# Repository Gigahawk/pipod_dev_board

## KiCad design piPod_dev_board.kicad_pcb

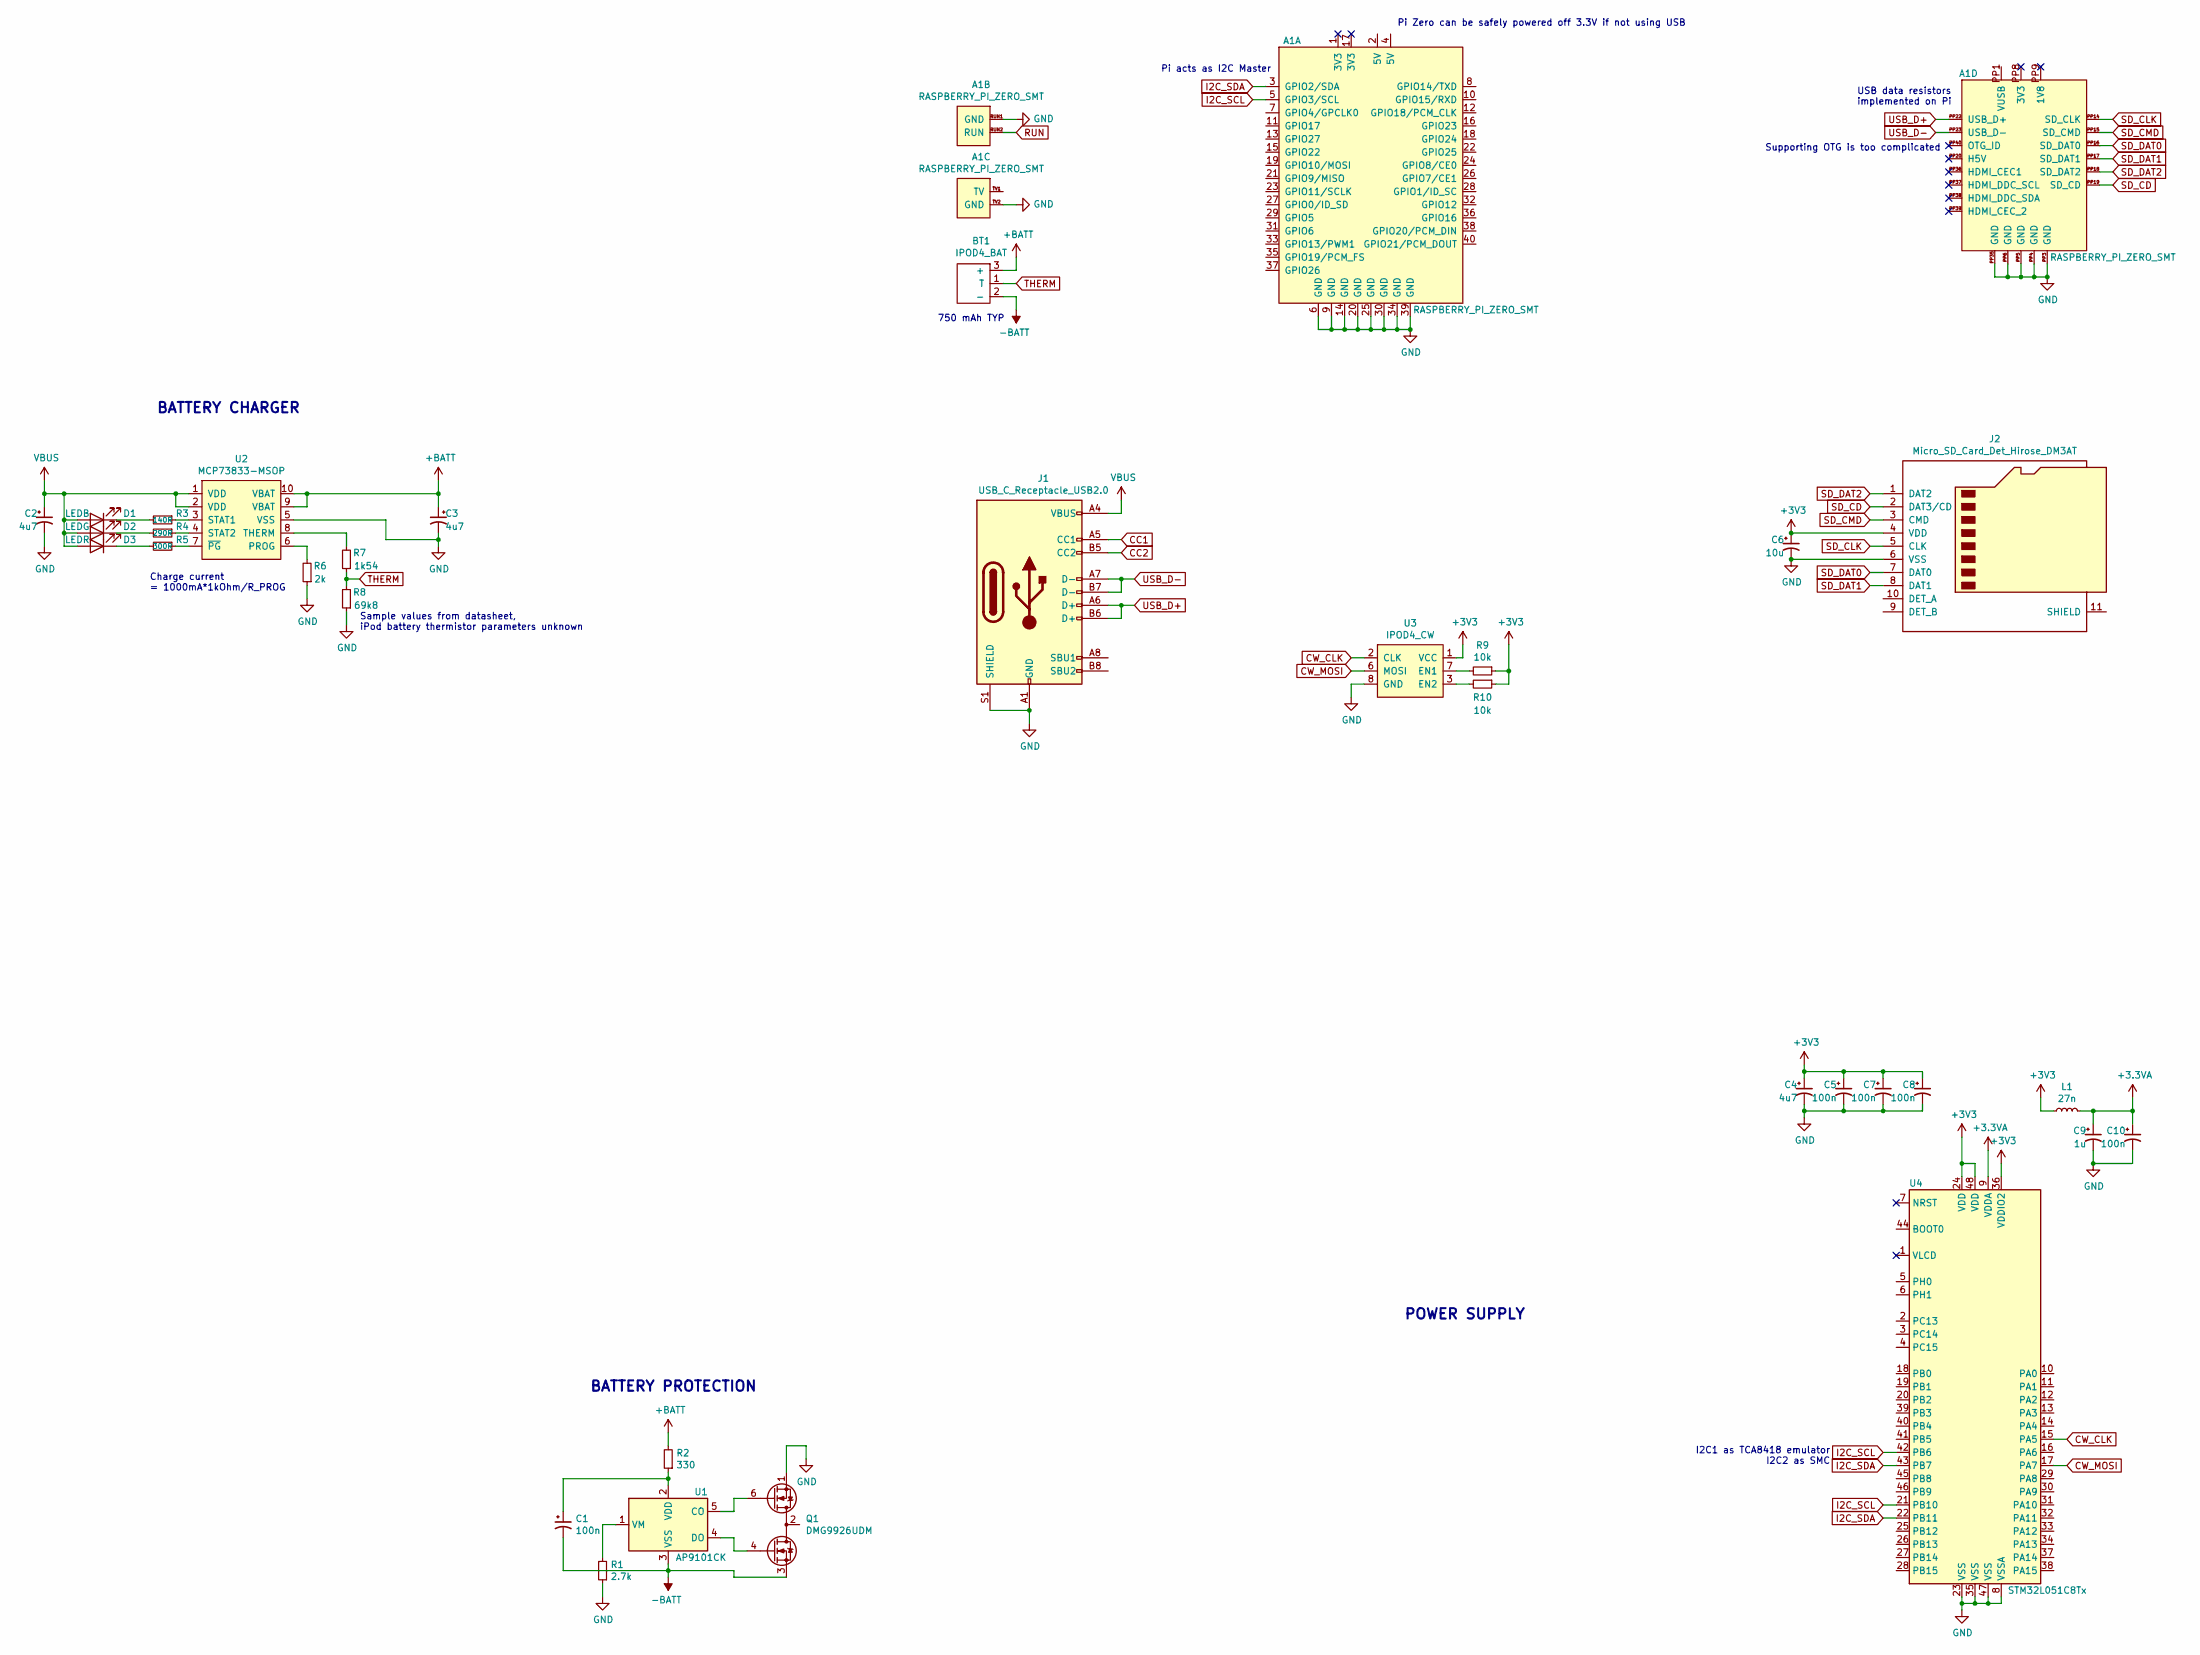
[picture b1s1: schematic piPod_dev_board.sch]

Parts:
A1: RASPBERRY_PI_ZERO_SMT; RASPI_ZERO_1_3_SMT_LOW_PROFILE
BT1: IPOD4_BAT; Molex_PicoBlade_53047-0310_1x03_P1.25mm_Vertical
C1, C5, C7, C8, C10: 100n; C_0805_2012Metric
C2, C3, C4: 4u7; C_0805_2012Metric
C6: 10u; C_0805_2012Metric
C9: 1u; C_0805_2012Metric
D1: LEDB
D2: LEDG
D3: LEDR
J1: USB_C_Receptacle_USB2.0; USB_C_Receptacle_GCT_USB4085
J2: Micro_SD_Card_Det_Hirose_DM3AT; microSD_HC_Hirose_DM3AT-SF-PEJM5
L1: 27n; L_0805_2012Metric
Q1: DMG9926UDM; SOT-23-6
R1: 2.7k; R_0805_2012Metric
R2: 330; R_0805_2012Metric
R3: 140R; R_0805_2012Metric
R4: 290R; R_0805_2012Metric
R5: 300R; R_0805_2012Metric
R6: 2k; R_0805_2012Metric
R7: 1k54; R_0805_2012Metric
R8: 69k8; R_0805_2012Metric
R9, R10: 10k; R_0805_2012Metric
U1: AP9101CK; SOT-23-5
U2: MCP73833-MSOP; MSOP-10_3x3mm_P0.5mm
U3: IPOD4_CW; SFV8R2STE1HLF
U4: STM32L051C8Tx; LQFP-48_7x7mm_P0.5mm

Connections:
+3.3VA: C9.1, C10.1, L1.2, U4.9 (VDDA)
+3V3: C4.1, C5.1, C6.1, C7.1, C8.1, J2.4 (VDD), L1.1, R9.1, R10.1, U3.1 (VCC), U4.24 (VDD), U4.36 (VDDIO2), U4.48 (VDD)
+BATT: BT1.3 (+), C3.1, R2.2, U2.9 (VBAT), U2.10 (VBAT)
-BATT: BT1.2 (-), C1.2, Q1.3 (S2), U1.3 (VSS)
CC1: J1.A5 (CC1)
CC2: J1.B5 (CC2)
CW_CLK: U3.2 (CLK), U4.15 (PA5)
CW_MOSI: U3.6 (MOSI), U4.17 (PA7)
GND: A1.6 (GND), A1.9 (GND), A1.14 (GND), A1.20 (GND), A1.25 (GND), A1.30 (GND), A1.34 (GND), A1.39 (GND), A1.PP3 (GND), A1.PP4 (GND), A1.PP5 (GND), A1.PP6 (GND), A1.PP35 (GND), A1.RUN1 (GND), A1.TV2 (GND), C2.2, C3.2, C4.2, C5.2, C6.2, C7.2, C8.2, C9.2, C10.2, J1.A1 (GND), J1.A12 (GND), J1.B1 (GND), J1.B12 (GND), J1.S1 (SHIELD), J2.6 (VSS), Q1.1 (D1), R1.1, R6.1, R8.1, U2.5 (VSS), U3.8 (GND), U4.8 (VSSA), U4.23 (VSS), U4.35 (VSS), U4.47 (VSS)
I2C_SCL: A1.5 (GPIO3/SCL), U4.21 (PB10), U4.42 (PB6)
I2C_SDA: A1.3 (GPIO2/SDA), U4.22 (PB11), U4.43 (PB7)
unnamed: C1.1, R2.1, U1.2 (VDD)
unnamed: D1.1 (K), R3.2
unnamed: D2.1 (K), R4.2
unnamed: D3.1 (K), R5.2
unnamed: Q1.2 (S1/D2), Q1.5 (S1/D2)
unnamed: Q1.4 (G2), U1.4 (DO)
unnamed: Q1.6 (G1), U1.5 (CO)
unnamed: R1.2, U1.1 (VM)
unnamed: R3.1, U2.3 (STAT1)
unnamed: R4.1, U2.4 (STAT2)
unnamed: R5.1, U2.7 (~PG)
unnamed: R6.2, U2.6 (PROG)
unnamed: R7.2, U2.8 (THERM)
unnamed: R9.2, U3.7 (EN1)
unnamed: R10.2, U3.3 (EN2)
RUN: A1.RUN2 (RUN)
SD_CD: A1.PP19 (SD_CD), J2.2 (DAT3/CD)
SD_CLK: A1.PP14 (SD_CLK), J2.5 (CLK)
SD_CMD: A1.PP15 (SD_CMD), J2.3 (CMD)
SD_DAT0: A1.PP16 (SD_DAT0), J2.7 (DAT0)
SD_DAT1: A1.PP17 (SD_DAT1), J2.8 (DAT1)
SD_DAT2: A1.PP18 (SD_DAT2), J2.1 (DAT2)
THERM: BT1.1 (T), R7.1, R8.2
USB_D+: A1.PP22 (USB_D+), J1.A6 (D+), J1.B6 (D+)
USB_D-: A1.PP23 (USB_D-), J1.A7 (D-), J1.B7 (D-)
VBUS: C2.1, D1.2 (A), D2.2 (A), D3.2 (A), J1.A4 (VBUS), J1.A9 (VBUS), J1.B4 (VBUS), J1.B9 (VBUS), U2.1 (VDD), U2.2 (VDD)

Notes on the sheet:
750 mAh TYP
BATTERY CHARGER
BATTERY PROTECTION
USB data resistors implemented on Pi
Supporting OTG is too complicated
Pi acts as I2C Master
I2C1 as TCA8418 emulator I2C2 as SMC
POWER SUPPLY
Charge current = 1000mA*1kOhm/R_PROG
Sample values from datasheet, iPod battery thermistor parameters unknown
Pi Zero can be safely powered off 3.3V if not using USB

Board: 2 copper layers, 30 parts (0 on the bottom side), 31 nets, no tracks yet.

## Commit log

2021-05-04 Add base library
2021-05-04 Start schematic, create power management circuitry
2021-06-02 Update submodule
2021-06-02 Redo power supply, switch to STM32 for SMC
2021-06-02 Switch RPi footprint to THT
